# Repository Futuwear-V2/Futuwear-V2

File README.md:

# Futuwear-V2
Protopaja 2017 group 11

Smart clothing motion capture shirt using ESP32 microcontroller and MPU-9250 IMUs.

To install the Arduino code on your ESP32, you need https://github.com/espressif/arduino-esp32 and the provided libraries. If you use the schematic, please note that the EN and IO0 pins need to be connected to ground when you upload the code to the device.

Guide on how to setup the server in /Server/README.md

Promotional website in /Nettisivu

Group members:
Jere Pylkkänen
Bruce Clayhills
Elliot Kölhi

https://protopaja.aalto.fi/futuricec/

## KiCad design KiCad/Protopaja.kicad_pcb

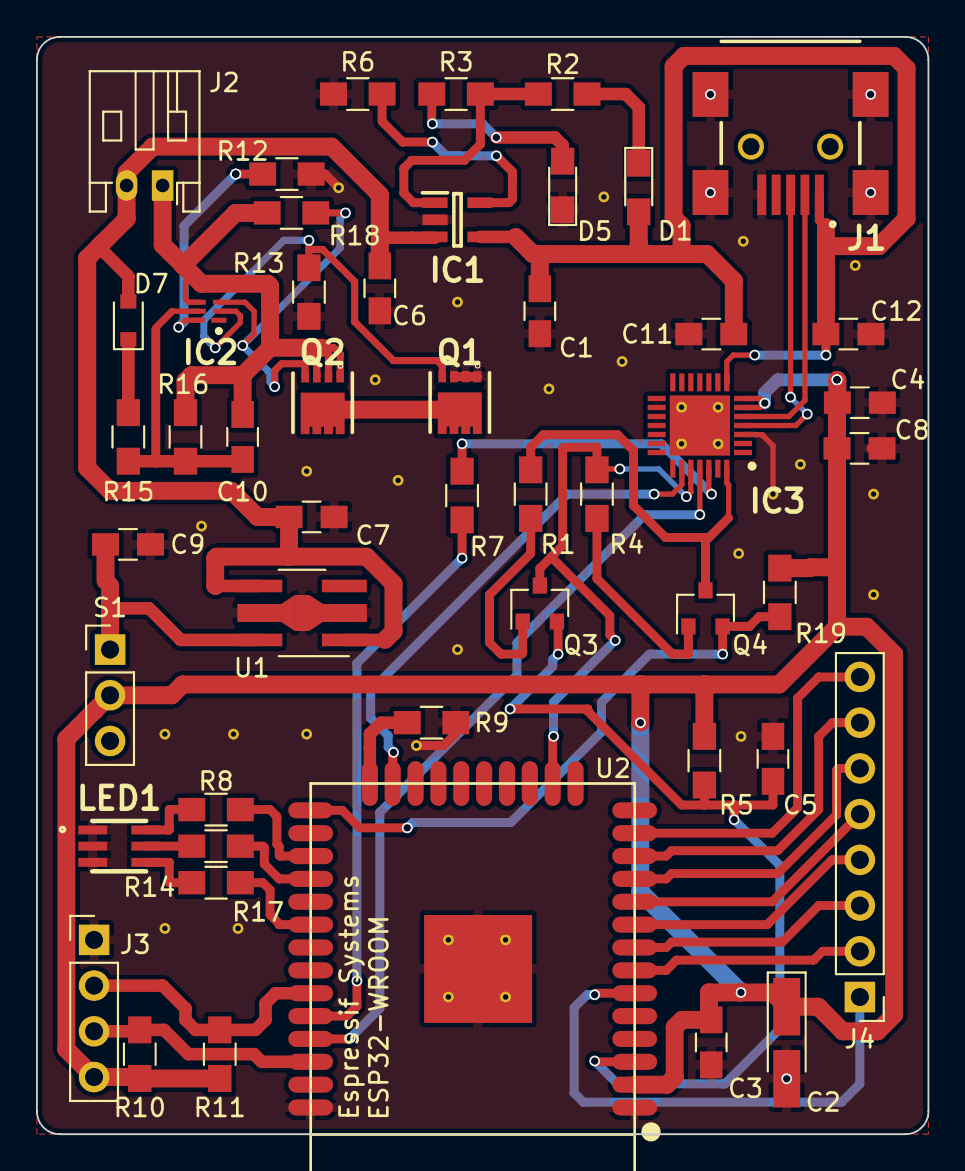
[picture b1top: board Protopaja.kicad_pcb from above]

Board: 2 copper layers, 49.5 x 61.0 mm, 49 parts (0 on the bottom side), 45 nets.

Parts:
C1, C4, C6, C11: 10uF; C_0805_HandSoldering
C2: 100uF-TTL; CP_Tantalum_Case-A_EIA-3216-18_Hand
C3, C7: 1uF; C_0805_HandSoldering
C5: 1nF; C_0805_HandSoldering
C8, C10, C12: 0.1uF; C_0805_HandSoldering
C9: 2uF; C_0805_HandSoldering
D1, D5: LED; LED_0805_HandSoldering
D7: D; D_0805
IC1: MCP73831T-2ATI_OT; SOT95P270X145-5N
IC2: BQ29733DSER; DSE_(S-PWSON-N6)
IC3: CP2102-GM; QFN50P500X500X100-29N
J1: USB_OTG; 10033526-XXX1XX
J2: B2B-PH-K-S(LF)(SN); JST_PH_S2B-PH-K_02x2.00mm_Angled
J3: CONN_01X04; Pin_Header_Straight_1x04_Pitch2.54mm
J4: CONN_01X08; Pin_Header_Straight_1x08_Pitch2.54mm
LED1: ASMT-YTC7-0AA02
Q1, Q2: CSD17575Q3; CSD16327
Q3, Q4: PBSS4120T; SOT-23
R1, R4, R5: 12KΩ; R_0805_HandSoldering
R2, R3: 1KΩ; R_0805_HandSoldering
R6: 2KΩ; R_0805_HandSoldering
R7: 470Ω; R_0805_HandSoldering
R8, R14: 40Ω; R_0805_HandSoldering
R9: 5KΩ; R_0805_HandSoldering
R10, R11: 10KΩ; R_0805_HandSoldering
R12: 2.2KΩ; R_0805_HandSoldering
R13, R18: 5MΩ; R_0805_HandSoldering
R15: 330Ω; R_0805_HandSoldering
R16: 1MΩ; R_0805_HandSoldering
R17: 240Ω; R_0805_HandSoldering
R19: R_0805_HandSoldering
S1: 09.03201.02; Pin_Header_Straight_1x03_Pitch2.54mm
U1: XC6210B332PR; SOT89-5_Housing_Handsoldering
U2: ESP32-WROOM

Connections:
+3V3: C2.1, C3.1, C4.1, C8.1, IC3.6, IC3.7, J3.4, R5.1, R10.2, R11.1, R19.2, S1.2, U2.2
+BATT: C6.1, C7.1, D7.2, IC1.3, J2.2, U1.1, U1.4
/-BATT: C10.2, IC2.4, J2.1, Q2.1, Q2.2, Q2.3, R16.2, R18.2
/CTS: IC3.23, U2.23
/DTR: IC3.28, Q4.3, R1.1
/EN: C5.1, Q3.2, R5.2, U2.3
/GPIO14: J4.8, U2.13
/GPIO16: R8.1, U2.27
/GPIO17: R14.2, U2.28
/GPIO18: R17.2, U2.30
/GPIO25: J4.5, U2.10
/GPIO26: J4.6, U2.11
/GPIO27: J4.7, U2.12
/GPIO32: J4.3, U2.8
/GPIO33: J4.4, U2.9
/GPIO34: J4.1, U2.6
/GPIO35: J4.2, U2.7
/IO0: Q4.2, R19.1, U2.25
/IO13: IC3.24, Q3.3, R4.1, U2.16
/RXD: IC3.25, U2.35
/RXD0: R7.2, U2.34
/SCL: J3.3, R10.1, U2.36
/SDA: J3.2, R11.2, U2.33
D+: IC3.4, J1.3
D-: IC3.5, J1.2
GND: C1.2, C2.2, C3.2, C4.2, C5.2, C6.2, C7.2, C8.2, C9.2, C11.2, C12.2, D5.1, IC1.2, IC3.3, IC3.29, J1.5, J1.6, J1.7, J1.8, J1.9, J3.1, LED1.1, LED1.2, LED1.3, Q1.1, Q1.2, Q1.3, R6.2, R9.2, R12.1, R13.2, U1.2, U2.1, U2.38, U2.39
unnamed: C9.1, S1.1, U1.5
unnamed: C10.1, IC2.5, R15.1, R16.1
unnamed: D1.1, R2.1
unnamed: D5.2, R3.2
unnamed: D7.1, R15.2
unnamed: IC1.1, R2.2, R3.1
unnamed: IC1.5, R6.1
unnamed: IC2.2, Q1.4, R13.1
unnamed: IC2.3, Q2.4, R18.1
unnamed: IC2.6, R12.2
unnamed: IC3.26, R7.1
unnamed: LED1.4, R17.1
unnamed: LED1.5, R14.1
unnamed: LED1.6, R8.2
unnamed: Q1.5, Q1.6, Q1.7, Q1.8, Q1.9, Q2.5, Q2.6, Q2.7, Q2.8, Q2.9
unnamed: Q3.1, R1.2
unnamed: Q4.1, R4.2
unnamed: R9.1, U2.24
USB_IN: C1.1, C11.1, C12.1, D1.2, IC1.4, IC3.8, J1.1

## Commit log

2017-08-08 Website
2017-08-14 Changed comments and a photo also added text
2017-08-14 Cleaned up the folder and moved stuff around. Fixed the probelms with the code and made the clickable button open a new tab.
2017-08-14 Improved the How it works page remarkably and added photos etc.
2017-08-15 Added empty file
2017-08-15 Added a lot of new stuff and improved previous stuff... Like new photos and svg file and everything.
2017-08-15 Added stuff and made it better, fixed website error
2017-08-16 Changed the font awesome css files to the new updated version and changed the color of the pages and created links and tidied everything up
2017-08-16 Added the favicon icons and other stuff. Changed the apperance of the sites and decluttered the sites
2017-08-16 Changed the background color in the main.css file to white.
2017-08-16 Changed the window where the HTML5up page opens to.
2017-08-16 Added more text to how it works and stuff.
2017-08-17 Added torso demo
2017-08-17 Changed the background to a picture and added the mysterious button link.
2017-08-17 Made a lot of improvements and added photos....
2017-08-17 Did some stuff can't even remember anymore.
2017-08-19 Added a photo and fixed text
2017-08-19 Added text etc.
2017-08-21 Modified files
2017-08-22 Added photos and a lot of text to the how it works page.
2017-08-22 Made some improvements and yall
2017-08-23 Added Arduino and server code
2017-08-23 Added a bunch of stuff
2017-08-23 Added pictures for Jere and Elliot and some text.
2017-08-23 actually added the pictures
2017-08-23 Did some shit and finalised the website....
2017-08-23 Added KiCad files.
2017-08-29 3D Enclosures added
2017-08-29 Rename IMU enclosure final.stl to IMU enclosure early.stl
2017-08-29 Sorted and renamed files
2017-08-29 Added some comments
2017-09-19 Added the final report and updated KiCad files
2017-10-02 Expanded readmes
2017-10-02 Added Arduino readme
